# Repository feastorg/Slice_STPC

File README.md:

# Slice STPC

## Introduction

Stepper motor controller Slice for BREADS-compatible systems.
This Slice is a carrier board for the [Stepper_card](https://github.com/IanVDS/stepper_card) board. It can carry up to four stepper cards, each with a DRV8825 stepper driver with microstepping and SPI pins for encoder reading.

## Usage

- Motor supply: 12-24 V on J1, up to 6 A total for the four cards.
- The motors only get power while the bus e-stop is high. A fault (over-current,
  over-voltage) latches the supply off until the e-stop or the power is cycled;
  GPIO5 reads low while latched.
- The bus jumpers JP1-JP4 are bridged by default; cut one to isolate that bus line from the Pico.

## Documentation

Please refer to the [docs](/docs) for more info.

---

<div align="center">
  
</div>

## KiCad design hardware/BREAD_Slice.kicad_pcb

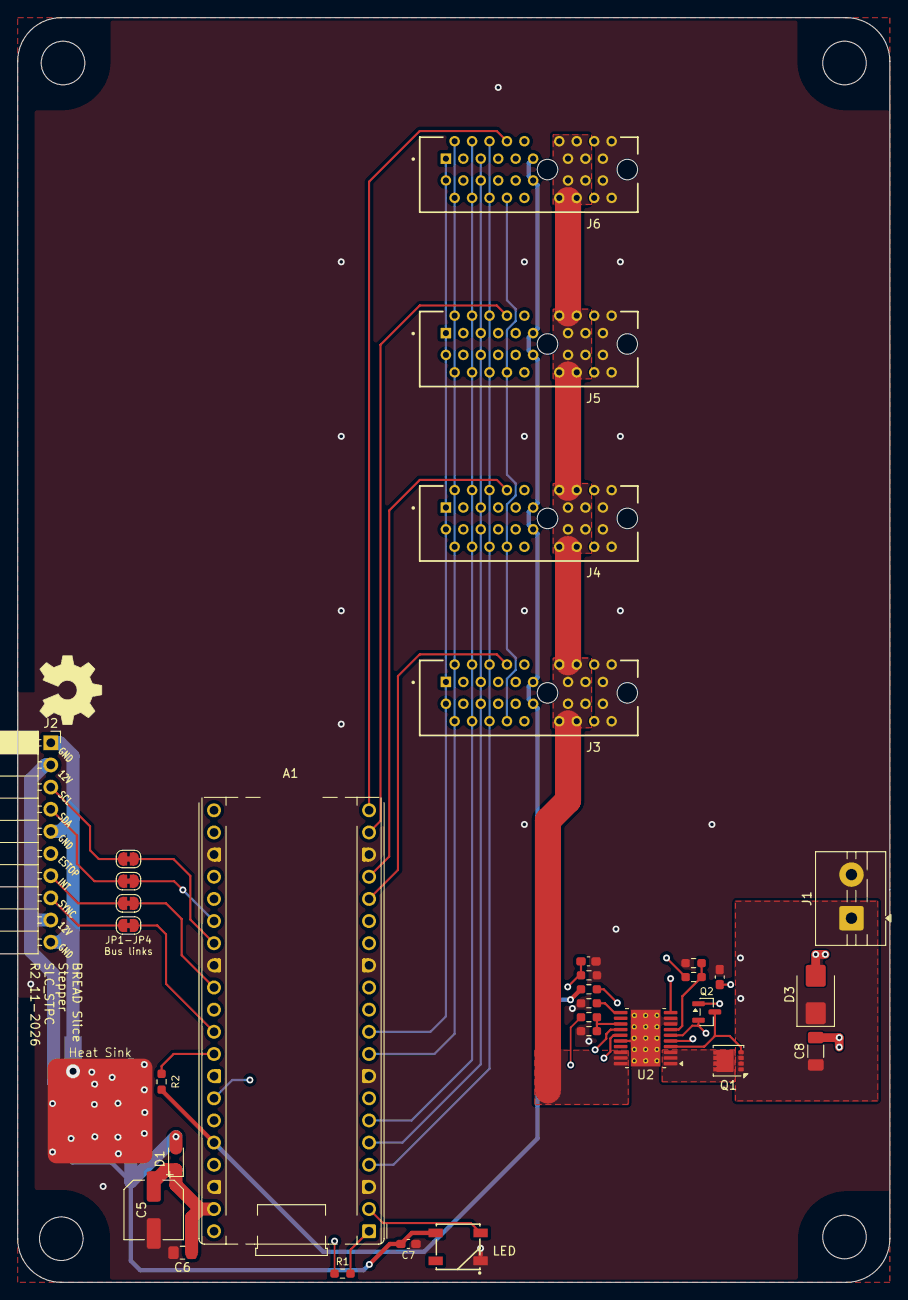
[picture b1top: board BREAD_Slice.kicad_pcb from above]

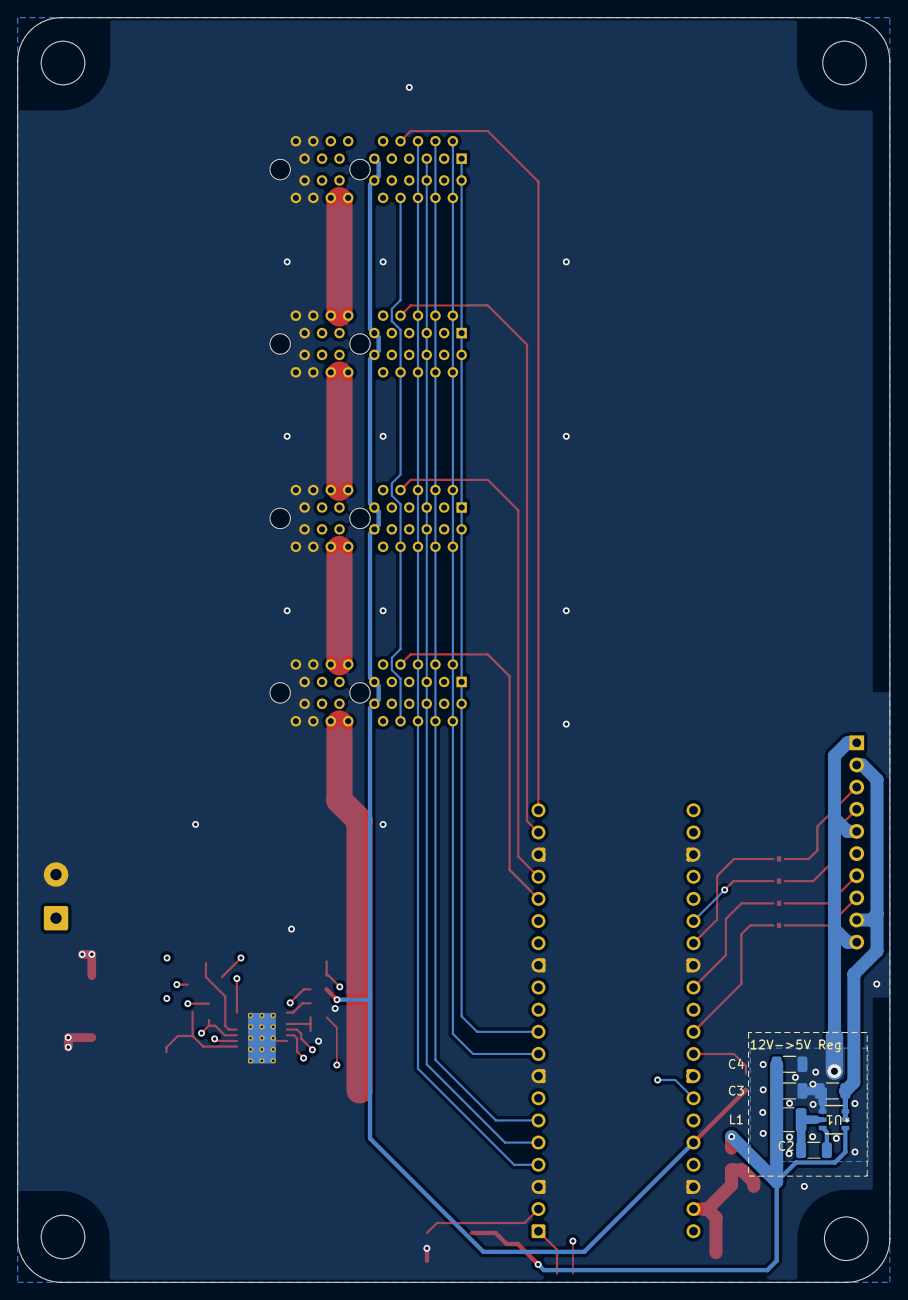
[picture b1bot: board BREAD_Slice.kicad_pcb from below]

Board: 4 copper layers, 100.0 x 145.0 mm, 45 parts (7 on the bottom side), 48 nets.

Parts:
A1: RaspberryPi_Pico; RaspberryPi_Pico_Common_THT
C1: 10u; C_1206_3216Metric
C2: 100nF; C_1206_3216Metric
C3, C4: 22uF; C_1206_3216Metric
C5: 47u 25V; CP_Elec_6.3x7.7
C6: 0.1u; C_0805_2012Metric_Pad1.18x1.45mm_HandSolder
C7: 100n; C_0603_1608Metric_Pad1.08x0.95mm_HandSolder
C8: 1u 50V X7R; C_1206_3216Metric_Pad1.33x1.80mm_HandSolder
C9: 47n; C_0603_1608Metric_Pad1.08x0.95mm_HandSolder
C10: 10n; C_0603_1608Metric_Pad1.08x0.95mm_HandSolder
D1: BAT54WS-7-F; D_SOD-323_HandSoldering
D2: WS2812B_5050; WS2812-5050-4PIN
D3: SM6T33A; D_SMB
H1, H2, H3, H4: MountingHole; MountingHole_5mm
HS1: Heatsink_Pad; Thermal_Pad
J1: Screw_Terminal_01x02; TerminalBlock_MaiXu_MX126-5.0-02P_1x02_P5.00mm
J2: Conn_01x10_Socket; PinSocket_1x10_P2.54mm_Horizontal
J3, J4, J5, J6: PCIE-036-02-X-D-TH; SAMTEC_PCIE-036-02-X-D-TH
JP1: I2C_CLK bus link; SolderJumper-2_P1.3mm_Bridged_RoundedPad1.0x1.5mm
JP2: I2C_DAT bus link; SolderJumper-2_P1.3mm_Bridged_RoundedPad1.0x1.5mm
JP3: INT bus link; SolderJumper-2_P1.3mm_Bridged_RoundedPad1.0x1.5mm
JP4: SYNC bus link; SolderJumper-2_P1.3mm_Bridged_RoundedPad1.0x1.5mm
L1: 4.7uH; L_1210_3225Metric
NT1: NetTie_2; NetTie-2_SMD_Pad2.0mm
Q1: CSD19537Q3; VSON-8_3.3x3.3mm_P0.65mm_NexFET
Q2: BSS138; SOT-23
R1: 1k; R_0603_1608Metric_Pad0.98x0.95mm_HandSolder
R2, R6, R9: 10k; R_0603_1608Metric_Pad0.98x0.95mm_HandSolder
R3: 680k 1%; R_0603_1608Metric_Pad0.98x0.95mm_HandSolder
R4: 97.6k 1%; R_0603_1608Metric_Pad0.98x0.95mm_HandSolder
R5: 3.01k 1%; R_0603_1608Metric_Pad0.98x0.95mm_HandSolder
R7: 47k; R_0603_1608Metric_Pad0.98x0.95mm_HandSolder
R8: 17.8k 1%; R_0603_1608Metric_Pad0.98x0.95mm_HandSolder
Ref**: Val**; OSHW_Logo_8mm
U1: AP63205; SOIC_05WU-7_DIO
U2: TPS26630PWP; HTSSOP-20-1EP_4.4x6.5mm_P0.65mm_EP3.4x6.5mm_Mask2.96x2.96mm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

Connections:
+3V3: A1.36 (3V3), J3.A11, J3.B11, J4.A11, J4.B11, J5.A11, J5.B11, J6.A11, J6.B11, R2.1, R9.1
+5V: C3.2, C4.2, C7.1, D1.2 (A), D2.1 (VDD), L1.2, U1.1 (FB)
+12V: C1.2, J2.2, J2.9, U1.2 (EN), U1.3 (VIN)
/CIPO: A1.6 (GPIO4), J3.A4, J3.B4, J4.A4, J4.B4, J5.A4, J5.B4, J6.A4, J6.B4
/COPI: A1.5 (GPIO3), J3.A5, J3.B5, J4.A5, J4.B5, J5.A5, J5.B5, J6.A5, J6.B5
/CS0: A1.25 (GPIO19), J3.A3
/CS1: A1.24 (GPIO18), J4.A3
/CS2: A1.22 (GPIO17), J5.A3
/CS3: A1.21 (GPIO16), J6.A3
/DIR0: A1.16 (GPIO12), J3.A8
/DIR1: A1.17 (GPIO13), J4.A8
/DIR2: A1.19 (GPIO14), J5.A8
/DIR3: A1.20 (GPIO15), J6.A8
/ESTOP_BUS: J2.6, R1.1, R6.1
/MOT_FLT: A1.7 (GPIO5), R9.2, U2.15
/MOT_IMON: A1.34 (GPIO28_ADC2), C10.1, R8.1, U2.14
/SCLK: A1.4 (GPIO2), J3.A6, J3.B6, J4.A6, J4.B6, J5.A6, J5.B6, J6.A6, J6.B6
/STEP0: A1.15 (GPIO11), J3.A7
/STEP1: A1.14 (GPIO10), J4.A7
/STEP2: A1.12 (GPIO9), J5.A7
/STEP3: A1.11 (GPIO8), J6.A7
/Stepper_card/SCL: A1.10 (GPIO7), J3.A1, J3.B1, J4.A1, J4.B1, J5.A1, J5.B1, J6.A1, J6.B1
/Stepper_card/SDA: A1.9 (GPIO6), J3.A2, J3.B2, J4.A2, J4.B2, J5.A2, J5.B2, J6.A2, J6.B2
/VM_BGATE: Q1.4, Q2.3, U2.4
/VM_D: Q1.5, U2.1, U2.2, U2.3
/VM_DRV: Q2.1, U2.5
/VM_DVDT: C9.1, U2.10
/VM_ILIM: R5.1, U2.11
/VM_IN: C8.1, D3.1, J1.1, Q1.1, Q1.2, Q1.3, Q2.2, R3.1, U2.6
/VM_SHDN: R6.2, R7.1, U2.13
/VM_UVLO: R3.2, R4.1, U2.7
/nFAULT: A1.32 (GPIO27_ADC1), J3.B8, J4.B8, J5.B8, J6.B8, R2.2
/slice_template/ESTOP_MCU: A1.1 (GPIO0), R1.2
/slice_template/I2C0_CLK/GPIO21: A1.27 (GPIO21), JP1.2
/slice_template/I2C0_SDA/GPIO20: A1.26 (GPIO20), JP2.2
/slice_template/I2C_CLK: J2.3, JP1.1
/slice_template/I2C_DAT: J2.4, JP2.1
/slice_template/INT: J2.7, JP3.1
/slice_template/INT/GPIO22: A1.29 (GPIO22), JP3.2
/slice_template/LED: A1.2 (GPIO1), D2.4 (DIN)
/slice_template/SYNC: J2.8, JP4.1
/slice_template/SYNC/GPIO26: A1.31 (GPIO26_ADC0), JP4.2
/slice_template/VSYS: A1.39 (VSYS), C5.1, C6.1, D1.1 (K)
GND: A1.3 (GND), A1.8 (GND), A1.13 (GND), A1.18 (GND), A1.23 (GND), A1.28 (GND), A1.38 (GND), C1.1, C3.1, C4.1, C5.2, C6.2, C7.2, C8.2, C9.2, C10.2, D2.3 (VSS), D3.2, HS1.1, J1.2, J3.A16, J3.A17, J3.A18, J3.B16, J3.B17, J3.B18, J4.A16, J4.A17, J4.A18, J4.B16, J4.B17, J4.B18, J5.A16, J5.A17, J5.A18, J5.B16, J5.B17, J5.B18, J6.A16, J6.A17, J6.A18, J6.B16, J6.B17, J6.B18, NT1.1, R4.2, R5.2, R7.2, R8.2, U1.4 (GND), U2.8, U2.9, U2.16, U2.21
GNDPWR: J2.1, J2.5, J2.10, NT1.2
unnamed: C2.2, U1.6 (BST)
unnamed: C2.1, L1.1, U1.5 (SW)
VM: J3.A12, J3.A13, J3.A14, J3.A15, J3.B12, J3.B13, J3.B14, J3.B15, J4.A12, J4.A13, J4.A14, J4.A15, J4.B12, J4.B13, J4.B14, J4.B15, J5.A12, J5.A13, J5.A14, J5.A15, J5.B12, J5.B13, J5.B14, J5.B15, J6.A12, J6.A13, J6.A14, J6.A15, J6.B12, J6.B13, J6.B14, J6.B15, U2.18, U2.19, U2.20

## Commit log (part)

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2026-05-20 did schematic
2026-05-21 more routing
2026-05-22 finished initial routing
2026-05-22 added nFAULT line
2026-05-22 changed todo
2026-05-24 Fix pipeline and customize from template to STPC
    - Fix workflow org case: FEASTorg → feastorg (caused startup_failure)
    - Update all config/docs from TEMP_NANO_S2L-r2 template to STPC
    - Add root TODO.md with pipeline status and board dev tasks
2026-05-24 Update TODO with CI results
2026-05-24 Standardize TODO.md with Pass 1/Pass 2 structure
2026-06-11 Add slice.yaml manifest
